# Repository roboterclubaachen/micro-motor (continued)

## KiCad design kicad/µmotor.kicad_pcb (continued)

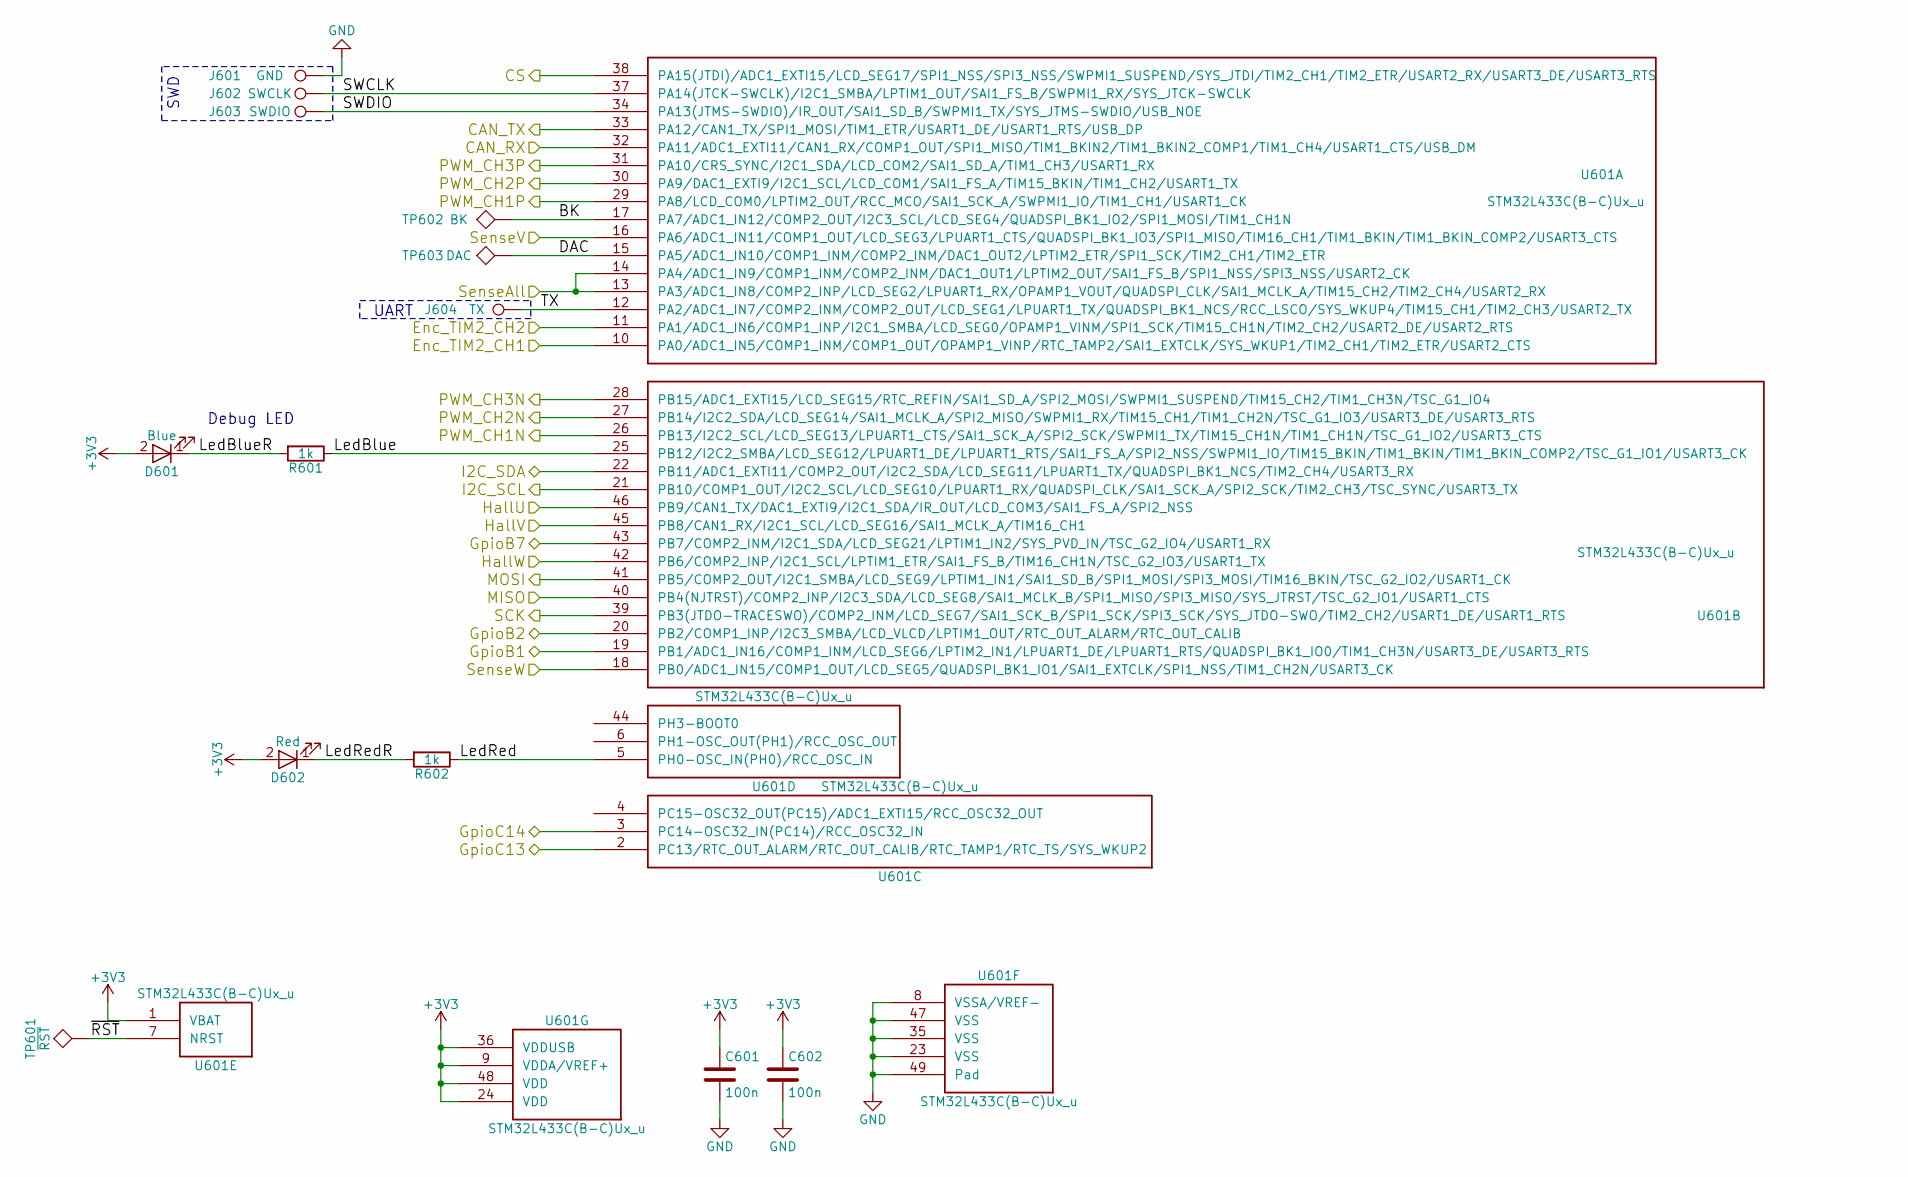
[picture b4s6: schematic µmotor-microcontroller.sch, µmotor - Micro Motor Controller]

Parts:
C601, C602: 100n; C_0603
D601: Blue; LED_0603
D602: Red; LED_0603
J601: GND; Measurement_Point_Round-SMD-Pad_Smaller_0.75mm
J602: SWCLK; Measurement_Point_Round-SMD-Pad_Smaller_0.5mm
J603: SWDIO; Measurement_Point_Round-SMD-Pad_Smaller_0.5mm
J604: TX; Measurement_Point_Round-SMD-Pad_Smaller_0.5mm
R601, R602: 1k; R_0603
TP601: ~RST; Measurement_Point_Round-SMD-Pad_Smaller_0.5mm
TP602: BK; Measurement_Point_Round-SMD-Pad_Smaller_0.5mm
TP603: DAC; Measurement_Point_Round-SMD-Pad_Smaller_0.5mm
U601: STM32L433C(B-C)Ux_u; QFN-48-1EP_7x7mm_Pitch0.5mm

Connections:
+3V3: C601.1, C602.1, D601.2 (A), D602.2 (A), U601.1 (VBAT), U601.9 (VDDA/VREF+), U601.24 (VDD), U601.36 (VDDUSB), U601.48 (VDD); also elsewhere on the board
/CAN/CAN_RX: U601.32 (PA11/ADC1_EXTI11/CAN1_RX/COMP1_OUT/SPI1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); also elsewhere on the board
/CAN/CAN_TX: U601.33 (PA12/CAN1_TX/SPI1_MOSI/TIM1_ETR/USART1_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); also elsewhere on the board
/Encoder/A: U601.10 (PA0/ADC1_IN5/COMP1_INM/COMP1_OUT/OPAMP1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); also elsewhere on the board
/Encoder/B: U601.11 (PA1/ADC1_IN6/COMP1_INP/I2C1_SMBA/LCD_SE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); also elsewhere on the board
/Microcontroller/BK: TP602.1, U601.17 (PA7/ADC1_IN12/COMP2_OUT/I2C3_SCL/LCD_SE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)
/Microcontroller/CS: U601.38 (PA15(JTDI)/ADC1_EXTI15/LCD_SEG17/SPI1_N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); also elsewhere on the board
/Microcontroller/DAC: TP603.1, U601.15 (PA5/ADC1_IN10/COMP1_INM/COMP2_INM/DAC1_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)
/Microcontroller/GpioB2: U601.20 (PB2/COMP1_INP/I2C3_SMBA/LCD_VLCD/LPTIM1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); also elsewhere on the board
/Microcontroller/GpioB7: U601.43 (PB7/COMP2_INM/I2C1_SDA/LCD_SEG21/LPTIM1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); also elsewhere on the board
/Microcontroller/GpioC14: U601.3 (PC14-OSC32_IN(PC14)/RCC_OSC32_IN); also elsewhere on the board
/Microcontroller/HallU: U601.46 (PB9/CAN1_TX/DAC1_EXTI9/I2C1_SDA/IR_OUT/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); also elsewhere on the board
/Microcontroller/HallV: U601.45 (PB8/CAN1_RX/I2C1_SCL/LCD_SEG16/SAI1_MCL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); also elsewhere on the board
/Microcontroller/HallW: U601.42 (PB6/COMP2_INP/I2C1_SCL/LPTIM1_ETR/SAI1_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); also elsewhere on the board
/Microcontroller/I2C_SCL: U601.21 (PB10/COMP1_OUT/I2C2_SCL/LCD_SEG10/LPUAR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); also elsewhere on the board
/Microcontroller/I2C_SDA: U601.22 (PB11/ADC1_EXTI11/COMP2_OUT/I2C2_SDA/LCD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); also elsewhere on the board
/Microcontroller/LedBlue: R601.1, U601.25 (PB12/I2C2_SMBA/LCD_SEG12/LPUART1_DE/LPU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)
/Microcontroller/LedBlueR: D601.1 (K), R601.2
/Microcontroller/LedRed: R602.1, U601.5 (PH0-OSC_IN(PH0)/RCC_OSC_IN)
/Microcontroller/LedRedR: D602.1 (K), R602.2
/Microcontroller/MISO: U601.40 (PB4(NJTRST)/COMP2_INP/I2C3_SDA/LCD_SEG8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); also elsewhere on the board
/Microcontroller/MOSI: U601.41 (PB5/COMP2_OUT/I2C1_SMBA/LCD_SEG9/LPTIM1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); also elsewhere on the board
/Microcontroller/SCK: U601.39 (PB3(JTDO-TRACESWO)/COMP2_INM/LCD_SEG7/S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); also elsewhere on the board
/Microcontroller/SWCLK: J602.1, U601.37 (PA14(JTCK-SWCLK)/I2C1_SMBA/LPTIM1_OUT/S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)
/Microcontroller/SWDIO: J603.1, U601.34 (PA13(JTMS-SWDIO)/IR_OUT/SAI1_SD_B/SWPMI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)
/Microcontroller/SenseAll: U601.13 (PA3/ADC1_IN8/COMP2_INP/LCD_SEG2/LPUART1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), U601.14 (PA4/ADC1_IN9/COMP1_INM/COMP2_INM/DAC1_O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); also elsewhere on the board
/Microcontroller/SenseV: U601.16 (PA6/ADC1_IN11/COMP1_OUT/LCD_SEG3/LPUART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); also elsewhere on the board
/Microcontroller/SenseW: U601.18 (PB0/ADC1_IN15/COMP1_OUT/LCD_SEG5/QUADSP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); also elsewhere on the board
/Microcontroller/TX: J604.1, U601.12 (PA2/ADC1_IN7/COMP2_INM/COMP2_OUT/LCD_SE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)
/Microcontroller/~RST: TP601.1, U601.7 (NRST); also elsewhere on the board
/Motor_Driver/ENABLE: U601.19 (PB1/ADC1_IN16/COMP1_INM/LCD_SEG6/LPTIM2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); also elsewhere on the board
/Motor_Driver/IN_U_N: U601.26 (PB13/I2C2_SCL/LCD_SEG13/LPUART1_CTS/SAI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); also elsewhere on the board
/Motor_Driver/IN_U_P: U601.29 (PA8/LCD_COM0/LPTIM2_OUT/RCC_MCO/SAI1_SC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); also elsewhere on the board
/Motor_Driver/IN_V_N: U601.27 (PB14/I2C2_SDA/LCD_SEG14/SAI1_MCLK_A/SPI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); also elsewhere on the board
/Motor_Driver/IN_V_P: U601.30 (PA9/DAC1_EXTI9/I2C1_SCL/LCD_COM1/SAI1_F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); also elsewhere on the board
/Motor_Driver/IN_W_N: U601.28 (PB15/ADC1_EXTI15/LCD_SEG15/RTC_REFIN/SA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); also elsewhere on the board
/Motor_Driver/IN_W_P: U601.31 (PA10/CRS_SYNC/I2C1_SDA/LCD_COM2/SAI1_SD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); also elsewhere on the board
GND: C601.2, C602.2, J601.1, U601.8 (VSSA/VREF-), U601.23 (VSS), U601.35 (VSS), U601.44 (PH3-BOOT0), U601.47 (VSS), U601.49 (Pad); also elsewhere on the board

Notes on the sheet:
SWD
UART
Debug LED

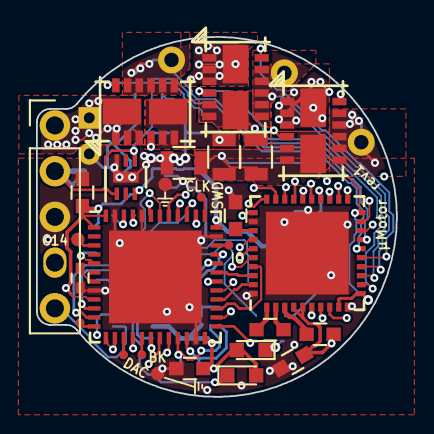
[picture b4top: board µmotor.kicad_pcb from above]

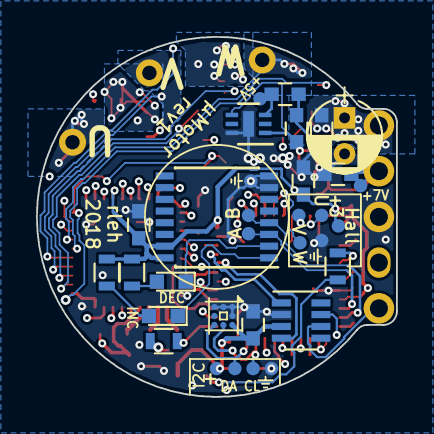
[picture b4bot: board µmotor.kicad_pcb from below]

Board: 4 copper layers, 20.0 x 20.0 mm, 62 parts (32 on the bottom side), 63 nets.

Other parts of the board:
C603: C; C_0402

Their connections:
/Microcontroller/~RST: C603.1; also elsewhere on the board
GND: C603.2; also elsewhere on the board

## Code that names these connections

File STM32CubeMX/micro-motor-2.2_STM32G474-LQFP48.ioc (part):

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Mcu.Name=STM32G474C(B-C-E)Tx
Mcu.Package=LQFP48
Mcu.UserName=STM32G474CETx
PA0.Signal=SharedAnalog_PA0
PA10.Signal=S_TIM1_CH3
PA11.Mode=Device
PA11.Signal=USB_DM
PA12.Mode=Device
PA12.Signal=USB_DP
PA13.Mode=Serial_Wire
PA13.Signal=SYS_JTMS-SWDIO
PA14.Mode=Serial_Wire
PA14.Signal=SYS_JTCK-SWCLK
PA15.GPIOParameters=GPIO_Label
PA15.GPIO_Label=SWITCH
PA15.Signal=GPIO_Input
PA2.Mode=ExternalOutput
PA2.Signal=COMP2_OUT
PA3.Signal=SharedAnalog_PA3
PA4.Signal=COMP_DAC11_group
PA5.Signal=COMP_DAC12_group
PA6.Mode=IN3-Single-Ended
PA6.Signal=ADC2_IN3
PA7.Mode=IN4-Single-Ended
PA7.Signal=ADC2_IN4
PA8.Signal=S_TIM1_CH1
PA9.Signal=S_TIM1_CH2
PB0.Signal=SharedAnalog_PB0
PB1.Mode=IN12-Single-Ended
PB1.Signal=ADC1_IN12
PB10.Mode=Synchronous
PB10.Signal=USART3_TX
PB11.Mode=Synchronous
PB11.Signal=USART3_RX
PB12.Mode=Synchronous
PB12.Signal=USART3_CK
PB13.Mode=Output Compare1 CH1 CH1N
PB13.Signal=TIM1_CH1N
PB14.Mode=Output Compare2 CH2 CH2N
PB14.Signal=TIM1_CH2N
PB15.Mode=Output Compare3 CH3 CH3N
PB15.Signal=TIM1_CH3N
PB2.Mode=IN12-Single-Ended
PB2.Signal=ADC2_IN12
PB3.Signal=S_TIM3_ETR
PB4.Signal=S_TIM3_CH1
PB5.Signal=S_TIM3_CH2
PB6.Mode=Asynchronous
PB6.Signal=USART1_TX
PB7.Mode=Asynchronous
PB7.Signal=USART1_RX
PB8-BOOT0.Mode=FDCAN_Activate
PB8-BOOT0.Signal=FDCAN1_RX
PB9.Mode=FDCAN_Activate
PB9.Signal=FDCAN1_TX
PC13.GPIOParameters=GPIO_Label
PC13.GPIO_Label=HALL_U
PC13.Signal=GPIO_Input
PC14-OSC32_IN.GPIOParameters=GPIO_Label
PC14-OSC32_IN.GPIO_Label=HALL_V
PC14-OSC32_IN.Signal=GPIO_Input
PC15-OSC32_OUT.GPIOParameters=GPIO_Label
PC15-OSC32_OUT.GPIO_Label=HALL_W
PC15-OSC32_OUT.Signal=GPIO_Input
PF0-OSC_IN.GPIOParameters=GPIO_Label
PF0-OSC_IN.GPIO_Label=ENABLE
PF0-OSC_IN.Signal=GPIO_Output
PF1-OSC_OUT.GPIOParameters=GPIO_Label
PF1-OSC_OUT.GPIO_Label=CSb
PF1-OSC_OUT.Signal=GPIO_Output
RCC.HSE_VALUE=8000000
RCC.SYSCLKFreq_VALUE=170000000
RCC.SYSCLKSource=RCC_SYSCLKSOURCE_PLLCLK
board=custom

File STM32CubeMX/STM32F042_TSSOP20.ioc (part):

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Mcu.Name=STM32F042F6Px
Mcu.Package=TSSOP20
Mcu.UserName=STM32F042F6Px
PA0.Signal=S_TIM2_CH1_ETR
PA1.Signal=S_TIM2_CH2
PA11.Mode=Master
PA11.Signal=CAN_RX
PA12.Mode=Master
PA12.Signal=CAN_TX
PA13.Mode=Serial_Wire
PA13.Signal=SYS_SWDIO
PA14.Mode=Serial_Wire
PA14.Signal=SYS_SWCLK
PA2.Mode=Asynchronous
PA2.Signal=USART2_TX
PA3.Mode=Asynchronous
PA3.Signal=USART2_RX
PA4.Signal=S_TIM14_CH1
PA5.Mode=IN5
PA5.Signal=ADC_IN5
PA7.Mode=PWM Generation1 CH1N
PA7.Signal=TIM1_CH1N
PB1.Mode=PWM Generation3 CH3N
PB1.Signal=TIM1_CH3N
PB8.Mode=I2C
PB8.Signal=I2C1_SCL
PF0-OSC_IN.Mode=I2C
PF0-OSC_IN.Signal=I2C1_SDA

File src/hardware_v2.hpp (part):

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};

namespace Ui {
	using LedRed		= GpioA4; // DAC1
	using LedGreen		= GpioA5; // DAC2

	using DebugUartTx	= GpioB6;
	using DebugUartRx	= GpioB7;
	using DebugUart		= Usart1;
	static constexpr uint32_t DebugUartBaudrate = 460800_Bd;

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
	using MotorTimer	= Timer1;

	using HallU			= GpioC13;
	using HallV			= GpioC14;
	using HallW			= GpioC15;
	using HallPort		= SoftwareGpioPort<HallU, HallV, HallW>;

//	constexpr uint8_t HallInterruptPriority	= 4; // Please don't use pin change interrupts on hall pins! Danger!

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		static_assert(HallPort::number_of_ports == 1, "Hall pins must be at the same port to guarantee atomic read operations.");

		// Timer is not used for commutation
		// Bldc motor commutation is done using external gpio pin interrupts
		//HallPort::setInput(Gpio::InputType::PullUp);

		HallU::setInput(Gpio::InputType::PullUp);
		HallV::setInput(Gpio::InputType::PullUp);
		HallW::setInput(Gpio::InputType::PullUp);

		HallU::setInputTrigger(Gpio::InputTrigger::BothEdges);
		HallU::enableExternalInterrupt();
		HallU::enableExternalInterruptVector(HallInterruptPriority);
		HallV::setInputTrigger(Gpio::InputTrigger::BothEdges);
		HallV::enableExternalInterrupt();
		HallV::enableExternalInterruptVector(HallInterruptPriority);
		HallW::setInputTrigger(Gpio::InputTrigger::BothEdges);
		HallW::enableExternalInterrupt();
		HallW::enableExternalInterruptVector(HallInterruptPriority);
	}
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	inline void
	initialize()
	{
		GateDriverEnable::setOutput(Gpio::OutputType::PushPull);
		GateDriverEnable::set(false);
		GateDriver::initialize();

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}

namespace BackEmf {
	using BemfU		= GpioB0;
	using BemfV		= GpioA7;
	using BemfW		= GpioA5;

	// ... (TODO)
	inline void
	initialize()
	{
		// TODO
		BemfU::setInput(Gpio::InputType::Floating);
		BemfV::setInput(Gpio::InputType::Floating);
		BemfW::setInput(Gpio::InputType::Floating);
	}
}

namespace MotorCurrent {
	using SenseU	= GpioA0;
	using SenseV	= GpioA1;
	using SenseW	= GpioA3;
	using Adc = Adc1;

	using CompU = Comp3;
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}

namespace Sensor {
	using Switch		= GpioA15;

	//using Adc 			= Adc??
	using Ntc			= GpioB1; // ADC1_IN12 or ADC3_IN1
	using Vsupply		= GpioB2; // ADC2_IN12

	inline void
	initialize()
	{
		// external pull-up
		Switch::setInput(Gpio::InputType::Floating);
		Ntc::setAnalogInput();
		Vsupply::setAnalogInput();
		
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	inline void
	initialize()
	{
		Can::connect<CanRx::Rx, CanTx::Tx>(Gpio::InputType::PullUp);
		Can::initialize<SystemClock, CanBaudrate>(9);
	}
}
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
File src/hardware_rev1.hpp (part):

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};

namespace Ui {
	using LedRed		= GpioInverted<GpioH0>;
	using LedBlue		= GpioInverted<GpioB12>;

	using PadC14		= GpioC14;
	using PadBrk		= GpioA7;
	using PadDac		= GpioA5;

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	inline void
	initialize()
	{
		LedRed::setOutput(modm::Gpio::High);
		LedBlue::setOutput(modm::Gpio::High);

		PadC14::setInput(Gpio::InputType::PullUp);

		DebugUart::connect<DebugUartTx::Tx>();
		DebugUart::initialize<systemClock, DebugUartBaudrate>(12);
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
	using MotorTimer	= Timer1;

	using HallU			= GpioB9;
	using HallV			= GpioB8;
	using HallW			= GpioB6;
	using HallPort		= SoftwareGpioPort<HallU, HallV, HallW>;

	constexpr uint8_t HallInterruptPriority	= 4;
	constexpr uint16_t MaxPwm{0x2FFu}; // 10 bit PWM
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		static_assert(HallPort::number_of_ports == 1, "Hall pins must be at the same port to guarantee atomic read operations.");

		// Timer is not used for commutation
		// Bldc motor commutation is done using external gpio pin interrupts
		HallPort::setInput(Gpio::InputType::PullUp);

		HallU::setInputTrigger(Gpio::InputTrigger::BothEdges);
		HallU::enableExternalInterrupt();
		HallU::enableExternalInterruptVector(HallInterruptPriority);
		HallV::setInputTrigger(Gpio::InputTrigger::BothEdges);
		HallV::enableExternalInterrupt();
		HallV::enableExternalInterruptVector(HallInterruptPriority);
		HallW::setInputTrigger(Gpio::InputTrigger::BothEdges);
		HallW::enableExternalInterrupt();
		HallW::enableExternalInterruptVector(HallInterruptPriority);
	}
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
namespace MotorBridge {
	using GateDriverEnable	= GpioB1;
	using GateDriverFault	= GpioInverted<GpioB2>;

	struct GateDriver
	{
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	inline void
	initialize()
	{
		GateDriverEnable::setOutput(Gpio::OutputType::PushPull);
		GateDriverEnable::set(false);

		GateDriverFault::setInput(Gpio::InputType::PullUp);

		GateDriver::initialize();

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}

namespace MotorCurrent {
	using SenseCal	= GpioB7;

	using SenseAll	= GpioA4;
	using SenseV	= GpioA6;
	using SenseW	= GpioB0;
	using Adc = Adc1;

	using CurrentAll	= GpioA3; // Shorted to GpioA4 on PCB
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	inline void
	initialize()
	{
		SenseCal::setOutput(Gpio::OutputType::PushPull);
		SenseCal::set(false);

		Adc::initialize(Adc::ClockMode::SynchronousPrescaler1,
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	inline void
	initialize()
	{
		Can::connect<CanRx::Rx, CanTx::Tx>(Gpio::InputType::PullUp);
		Can::initialize<systemClock, CanBaudrate>(9);
	}
}
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
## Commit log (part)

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2017-09-14 add gitignore
2017-09-14 initial µmotor design
2017-09-14 add STM32CubeMX file, STM32F042 pinout
2018-01-05 added mic4606 lib
2018-01-05 add DRV8323S kicad symbol lib
2018-01-06 add generated (up-to-date) STM32 kicad symbol lib
2018-01-06 add STM32CubeMX file, STM32L432KC (UFQFPN32) pinout
2018-01-06 second design: STM32L432KC µC with DRV8323S gate driver and FDMD82xx FETs
2018-01-06 add STM32CubeMX file, STM32L433CCUx (UFQFPN48) pinout
2018-02-04 update µC pinout, motor driver, CubeMX, add 3V3 regulator and temperature sensor
2018-02-05 layout: components placed
2018-02-05 layout: export gerber
2018-02-05 layout: improvements and silkscreen
2018-02-05 layout: routing finished
2018-02-06 add DRV8323 input cap, improve board outline
2018-02-10 increase via and track sizes
2018-04-14 [software] Add abstraction layer (hardware_rev1.hpp)
2018-04-14 [software] OpenOCD config file
2018-04-14 [software] Test: Blink
2018-05-05 [software] replace xpcc with modm
2018-05-08 [software] Use Hsi16 oscilator instead of Msi (4MHz) | F_CPU=80MHz
2018-05-08 [software] test: blink two leds
2018-05-16 [software] hardware_rev1.hpp: Fix MISO pull-up
2018-05-16 [software] add Drv832x driver
2018-05-16 [software] add test: gatedriver
2018-05-22 [software] hardware.hpp: DebugUart baudrate 460800; Spi Miso external pull-up
2018-05-22 [software] Drv832x driver: fixes
2018-05-22 [software] test_gatedriver: DebugUart BlockIfFull
2018-05-22 [software] Drv832x driver reworked
2018-05-22 [software] test_gatedriver: adapt to new Drv832x driver
2018-05-29 [software] drv832x driver moved into modm framework
2018-07-05 [test] add can test
    retransmit incoming messages and increase idx
2018-07-06 [software] hardware.hpp: Can frequency
2018-07-08 [software] Update modm project.xml files
2018-07-08 Gitlab CI enabled
2018-07-10 [software] add test: DC motor
2018-07-11 [software] test DC motor: add ADC current measurement
2018-07-12 [software] add test: BLDC motor
2018-07-12 Add licenses
2018-07-12 Add README document
2018-08-10 [ci] add DC and BLDC motor test to CI
2018-08-10 [modm] Update for modm:build module renaming
2018-09-04 Fix BLDC commutation logic
2018-09-23 Remove unfinished DRV832x testboard
2018-09-23 Add macro-motor dev board schematic
2018-09-24 macro-motor: Finish dev board schematic
2018-09-24 macro-motor: PCB Layout
2018-09-24 macro-motor: PCB Layout finished, silkscreen
2018-09-24 macro-motor: Minor fixes
2018-09-25 macro-motor: add BOM (csv)
2019-09-20 micro-motor-v2: block diagram
2019-09-20 micro-motor-v2: block diagram updated
2019-09-20 micro-motor-v2: CubeMX mcu/pinout for STM32G474CE
2019-09-20 micro-motor-v2: CubeMX for STM32G474CE updated
2019-09-20 [kicad/lib] Update STM32 lib
2019-09-20 micro-motor-v2: Schematic continued
2019-09-20 micro-motor-v2: Fix DRV8323/DRV8320 libs
2019-09-20 micro-motor-v2: Schematic finished
2019-09-20 micro-motor-v2: layout: components placed
2019-09-23 micro-motor-v2: More capacitors, outline corners
2019-10-10 micro-motor-v2: Layout finished
2019-10-10 micro-motor-v2: Layout Silkscreen
2019-10-19 micro-motor-v2: BOM
2019-11-02 micro-motor-v2: KiCad iBom pick-and-place helper
2019-11-02 [software] add hardware_rev2.hpp
2019-11-02 Move micro-motor-v1 pcb to subfolder
2019-11-02 Remove gerber files
2021-07-31 Fix gitignore
2021-07-31 PCB: micro-motor-v2.1
    * Replace TPS82150 with LMZM23601
    * Add 1uF capacitor to STM32 VREFBUF output pin
    * Add RC filters (10nF / 10Ω) to encoder input
2021-11-17 Add KiBot config file
2021-11-17 Fix KiCAD lib file syntax for kibot
2021-11-19 micro-motor-v2: CubeMX clock configuration
2021-11-19 micro-motor-v2/software: HAL header and blink example
2021-11-19 micro-motor-v2: update test software
2021-11-19 micro-motor-v2: 3d model step file exported
2021-11-19 Use more lbuild!
2021-11-19 [sw][test] fix xml and includes for blinky
2021-11-19 [lbuild] remove unneccessary custom SConstruct; gen. by lbuild
2021-11-19 CI: update scripts
2021-11-19 micro-motor-v2: motor current sensing
2022-04-18 [test] Fix modm:build:info.git lbuild option
2022-04-18 Seperate debug uart init from dac/led init; fix all tests
2022-04-18 Fix bugs test applications
2022-04-18 Adapt hardware.hpp for use with librobots2
2022-04-18 Fix example build directories
2022-04-18 [test] Use librobots2 in FOC test
2022-04-18 Update CI docker image
2022-04-18 Fix functions call from library
2022-04-18 [test] WIP: add more comments to FOC example
2022-04-18 gitignore: vscode
2022-04-18 Fix pwm timer frequency
2022-04-18 Enable (Fd)Can interface
2022-04-18 WIP: CanOPEN application code
2022-04-18 [hardware] Use non-deprecated SysTickTimer init function
2022-04-18 Add BLDC turn open-loop example
2022-04-18 [test] WIP: FOC motor test
2022-04-18 Cleanup lbuild dependencies
    * Update list in common.lb (and sort it)
    * Therefore, remove those dep. modules from the tests
    * Add tests in build script for CI
2022-04-18 Separate UI::init.() fct - using leds either as IO or via DAC
2022-04-18 Make CAN test/example working
2022-04-18 [lbuild] Update repo file
2022-04-18 Hacked application for controlling 1 DC motor with motor-can
2022-09-19 Configure current limit comparator hysteresis
2022-10-16 BLDC block commutation example with canopen interface
2022-10-16 Fix reading hall state
2023-01-20 [canopen] Add new canopen and test module
2023-01-20 [canopen] Made velocity PID parameters writeable over can
2023-01-20 [canopen] Added tests for canopen bldc
2023-01-20 [canopen] Fixed include paths
2023-01-20 [canopen] Factored out address names
2023-01-20 [canopen] Moved test related stuff out of src
2023-01-20 [canopen] Remove duplicate plot_csv.py
2023-01-20 [canopen] Fix averaging negative numbers
2023-01-20 [canopen] Add rolling average to velocity
2023-01-20 [canopen] Remove unneccesary dependencies
2023-01-20 [canopen] Add on the fly velocity change
2023-01-20 [canopen] Start implementing Position PID
2023-01-20 [canopen] Removed duplicated average
2023-01-20 [canopen] Split handlers into multiple files
2023-01-21 [canopen] Move timer out of MotorControl
2023-01-21 [canopen] Properly implement Polarity factor
2023-01-21 [canopen] Replace Pos-Error with proper object
2023-01-24 [canopen] Refactoring
2023-01-25 [canopen] Change Protocol selection behaviour
2023-01-25 [canopen] Start implementing QuickStop
2023-01-25 [canopen] More refactoring, added loop time info
2023-01-31 [canopen] fix canopen_bldc_board
2023-03-24 [canopen] Remove commander specific eds
2023-03-25 [canopen]Remove some log spam
2023-03-25 [canopen] Update commander for modm-canopen
2023-03-26 [canopen] Implement basic heartbeat and identity provider
2023-03-27 [¢anopen] Fix modes not being updated correctly
2023-03-27 [canopen] Improve debug output
2023-03-28 [canopen] fix missing include in pwm protocol
2023-03-28 [canopen] send heartbeat faster
2023-04-07 [canopen] Fix deprecated copy warnings
2023-04-16 [src] Add function to read out hardware ID
2023-04-16 [app] assign boardID and nodeID based on hardwareID
2023-04-16 [app] Copy test_canopen_board to app
2023-04-16 [app] add hardware and bord id
2023-04-16 [app] Add more debug output (nodeID)
2023-04-20 [app] Add debug output to console
2023-04-24 Add spare micro motors to hardware
2023-04-24 Add Reset Register to reset motors
2023-04-24 Update canopen_objects
2023-04-24 Implement easy nodeID switching for testing
2023-04-24 Fix position Protocol not updating ctrl word
2023-04-24 Make test.sh close all instances on Ctrl+C
2023-04-26 Remove canopen_bldc_board
2023-04-26 Add canopen_bldc_hosted,_commander to build_tests
2023-04-26 Synchronize changes from alpha_motor
2023-05-01 [app] modify debug output
2023-05-01 Move motor independent stuff to its own repo
2023-05-03 Move scons dependency out of micro-motor.xml
2023-05-08 Move motor-canopen to librobots2
2023-05-09 Add MotorControl_t definition
2023-05-09 Change debug output
2023-05-11 canopen: disable error protocol
2023-05-11 canopen: support motor heartbeat
2023-05-13 app: restrict max current to 25%
2023-05-18 app: Current Control
2023-05-19 Fix adcs not returning values
2023-05-19 change plot csv
2023-05-22 app: decreased control-loop time
2023-05-22 chaneg modm-canopen module, implement sim current
2023-06-21 app: made current-control work somewhat
    fix inconsistent commutation
2023-07-11 made necessary changes for V2.2, missing DRC
2023-07-11 solved most critical DRC issues
2023-07-12 update canopen_bldc_commander
2023-07-25 commander: made position control work
2023-08-08 app/commander: Charge testing
2023-08-15 app: reenable timeout reset
2023-08-15 commander: Fix Object names
2023-09-26 Hopefully fix ADC initialization
2023-09-26 Support additional PDOs
2023-10-03 Update commander test program
2023-10-14 Change back to 4 PDOs, tune pPID
2023-10-14 Fix wrong current being set
2023-10-14 Test bldc_motor_current
2023-10-18 Remove debug prints
2023-10-31 Change to work with new motors
2023-12-09 Redordering in main
2023-12-12 Left shift reported positions by 12 bits
2024-02-11 Switch season2023 to submodules
2024-02-11 Remove rca-helper script from .gitlab-ci.yml
2024-02-11 Add new motor tuning test project
2024-02-11 Update bldc_hosted
2024-02-11 Add Eigen wrapper
2024-02-11 Refactor commander
2024-02-11 Continue implementing tuner
2024-02-12 Update to work with submodules
2024-02-12 Add CSV logging
2024-02-12 Change motor simulation
2024-02-16 Implement tuner algorithm fully (untested)
2024-02-20 Fix stupid error in relay_analyzer
2024-02-25 Make simulation work
2024-02-25 Move motor simulation to librobots2
2024-02-27 Add NixOS support
2024-02-28 Change modules to relative paths
2024-02-29 [motor-tuner] Fix State setup
2024-02-29 [canopen_bldc_hosted] Make logging togglable
2024-02-29 [canopen_bldc_hosted] Fix warning, update motor config
2024-02-29 [motor_tuner] Fix obviuous bugs in relay_analyzer
2024-03-03 [motor-tuner] Add WIP PID Parameter derivation
2024-03-04 [motor-tuner] Refactoring
2024-03-08 Take control timing from librobots2
2024-03-08 Reduce ADC integration time
2024-03-08 Fix outdated currentLimit definition
2024-03-08 Add simple relay analyzer for testing
2024-03-08 Update to use Hysteresis control
2024-03-08 Fix warnings
2024-03-11 Factor out state logic from MotorControl
2024-03-11 Add Git info to startup
2024-03-11 Update commader tool
2024-03-11 Update last references to old state
2024-03-12 Basically revert to PWM control
2024-03-19 Update librobots2
2024-03-23 Add option to select hardware version
2024-03-23 Add the first of the new micro-motors
2024-04-20 Actually use ADC W
2024-04-23 Change back to v2.1
2024-04-24 Use configurable ids
2024-06-06 Add test firmware stub
2024-06-06 [test-firmware] zero current test
2024-06-06 Move current computation into micro-motor.cpp
2024-06-06 Remove useless node id
2024-06-06 Change current limit test behaviour
2024-06-06 Fix waiting in test-firmware
2024-06-06 Add current limit test
2024-06-06 Test light load, and find motor parameters
2024-06-06 Fix test compilation
2024-06-11 Update flake
2024-06-28 Add test firmware to CI
2024-06-28 Clear break interrupt flag in test-firmware
2024-07-02 Ready for watney
2024-07-13 nixos: Update Flake
2024-08-08 [canopne_bldc_hosted] Change output filename
2024-08-08 Add real time plotting to canopen_bldc_hosted
2024-08-24 Formatting
2024-08-27 Update librobots
2024-10-02 Add encoder support
2024-11-21 Update modm
2024-11-21 Update librobots and modm-canopen
2024-11-22 [canopen_hosted] Fix hosted operation
2024-11-26 Update modm-canopen
2024-11-27 Disable motor if not NMT Operational
2024-11-27 [canopen_hosted] Shorten sleep
2025-01-19 Update Readme to address #4
2025-02-11 Add motor 18
2025-02-11 [CI] Setup gitea action CI
2025-02-11 [CI] WIP kicad CI
2025-02-11 [CI] Only run CI when relevant
2025-02-11 [CI] Add apt caching
2025-02-11 [CI] remove apt caching
2025-02-11 [kicad] Remove old backup files
2025-02-11 [CI] Remove prebuilt Kicad actions
2025-02-11 [CI] Fix artifacts
2025-02-11 [CI] Disable micro-motor-v1 CI(files are too old)
2025-02-11 [CI] Add more stuff to legacy CI
2025-02-11 [CI] Remove legacy from new kicad CI
2025-02-11 [CI] Add step generation
2025-02-11 [CI] Disable PDF generation on failed ERC with kicad 8
2025-02-11 [CI] Split Kibot config
2025-02-11 [CI] Consolidate Board layer PDFs to pages
2025-02-11 [CI] Fix CI trigger for Kicad
2025-02-11 [CI] Attempt to fix ERC
2025-02-12 [CI] Fix file name errors
2025-02-16 Update dependencies
